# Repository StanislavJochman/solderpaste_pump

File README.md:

# solderpaste_pump

This is solderpaste dispeser

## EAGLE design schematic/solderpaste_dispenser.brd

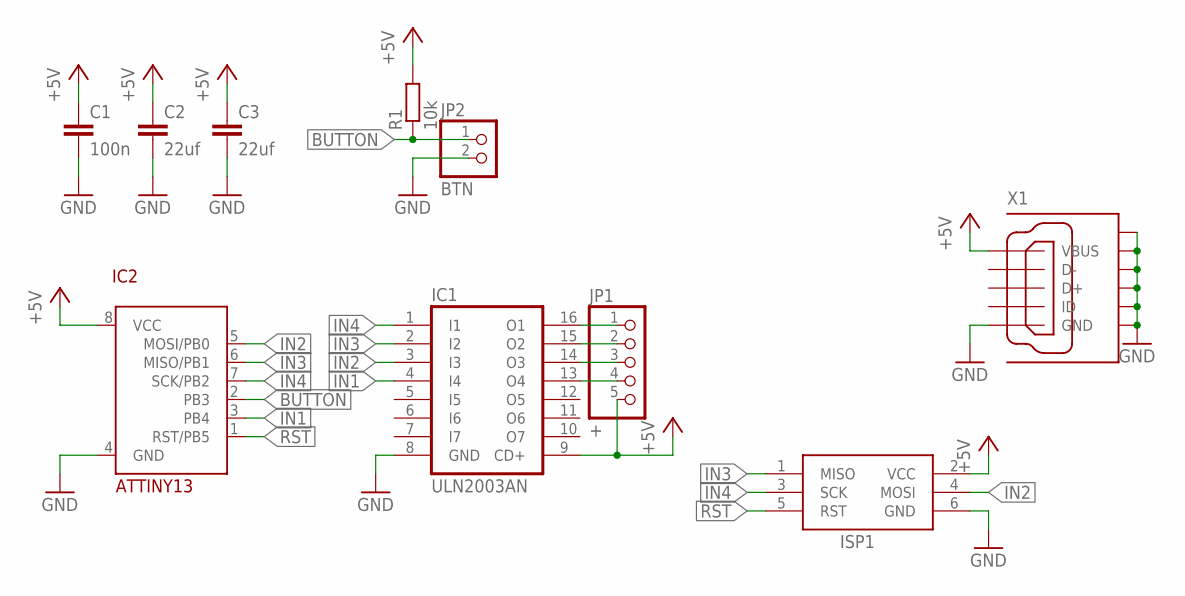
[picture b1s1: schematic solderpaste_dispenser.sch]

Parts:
C1: 100n; C1206
C2, C3: 22uf; C1206
IC1: ULN2003AN; DIL16
IC2: ATTINY13; SOIC8
ISP1: AVRISP-6; AVRISP
JP1: +; 1X05
JP2: BTN; 1X02
R1: 10k; M1206
X1: GHI-CONNECTORS_10118192-0001LF; GHI-CONNECTORS_10118192-0001LF(MICRO-USB-B-AMPHENOL-FCI)

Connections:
+5V: C1.1, C2.1, C3.1, IC1.9 (CD+), IC2.8 (VCC), ISP1.2 (VCC), JP1.5, R1.2, X1.VBUS
BUTTON: IC2.2 (PB3), JP2.1, R1.1
GND: C1.2, C2.2, C3.2, IC1.8 (GND), IC2.4 (GND), ISP1.6 (GND), JP2.2, X1.CGND1 (SGND1), X1.CGND2 (SGND2), X1.CGND3 (SGND3), X1.CGND4 (SGND4), X1.CGND5 (SGND5), X1.CGND6 (SGND6), X1.GND
IN1: IC1.4 (I4), IC2.3 (PB4)
IN2: IC1.3 (I3), IC2.5 (MOSI/PB0), ISP1.4 (MOSI)
IN3: IC1.2 (I2), IC2.6 (MISO/PB1), ISP1.1 (MISO)
IN4: IC1.1 (I1), IC2.7 (SCK/PB2), ISP1.3 (SCK)
unnamed: IC1.16 (O1), JP1.1
unnamed: IC1.15 (O2), JP1.2
unnamed: IC1.14 (O3), JP1.3
unnamed: IC1.13 (O4), JP1.4
RST: IC2.1 (RST/PB5), ISP1.5 (RST)

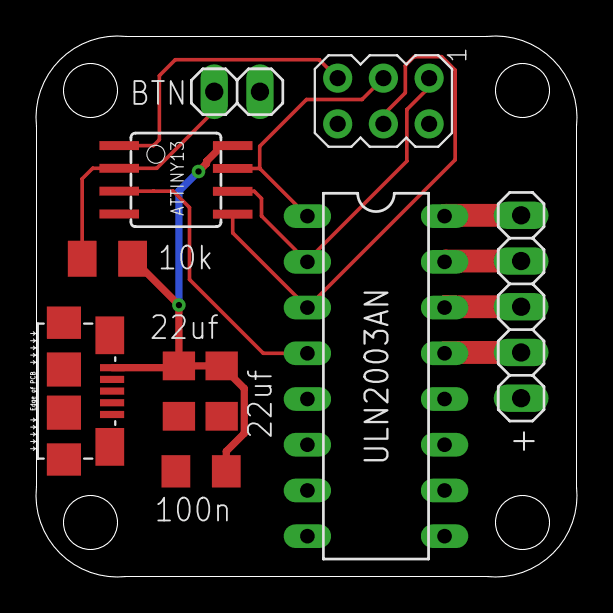
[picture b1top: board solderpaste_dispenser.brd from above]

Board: 2 copper layers, 30.1 x 30.1 mm, 10 parts (0 on the bottom side), 12 nets.
